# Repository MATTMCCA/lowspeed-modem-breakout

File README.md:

# DO NOT Screw with the telephone lines, the FCC will come after you...

(This IC dose have a transferable, Part 68 Registration. Since this board is not going to be evaluated for compliance, I advise you keep this puppy away from live phone lines.)

Hooking up unlicensed homebrew phone equipment is illegal, be smart, [just go buy a modem](https://www.newegg.com/p/2Z4-025W-02BE7).  

Could this be used with a Raspberry Pi or Arduino? Yes, Absolutely.  Just make sure you don't operate this device on the phone network without proper certs or permission from phone company (which I don't even think is a thing). 

[... I'm Serious](https://www.law.cornell.edu/uscode/text/47/227).

This may be a better [alt](https://www.tindie.com/products/theoldnet/rs232-serial-wifi-modem-for-vintage-computers-v3/).

# lowspeed-modem-breakout
Modem Module 2.4Kbps Data, BREAKOUT.

Not 56k, but it is an all in one solution with a super minimal part count.

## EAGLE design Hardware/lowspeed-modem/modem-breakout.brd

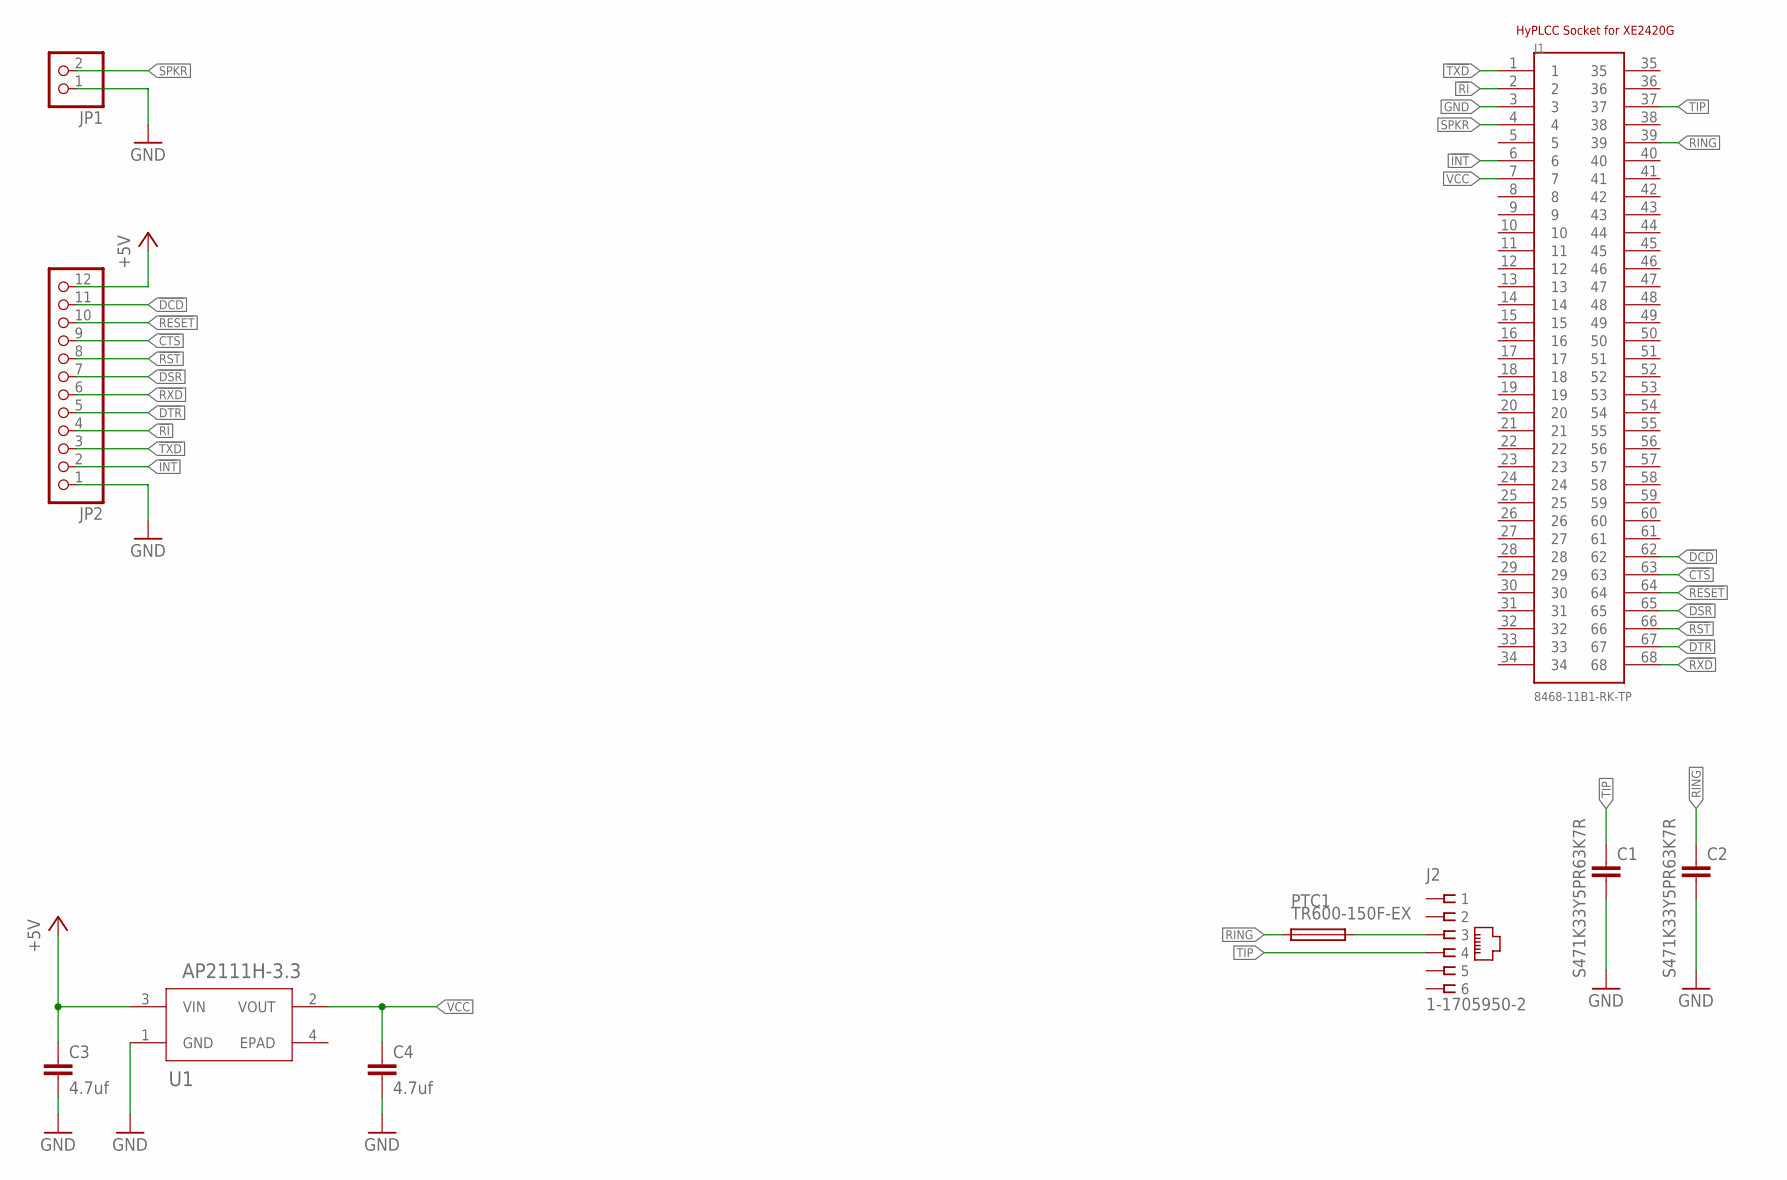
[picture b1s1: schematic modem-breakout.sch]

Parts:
C1, C2: S471K33Y5PR63K7R; C075-052X106
C3, C4: 4.7uf; C0805
J1: 8468-11B1-RK-TP; 3M_8468-11B1-RK-TP
J2: 1-1705950-2; RJ11-NO_SHIELD
JP1: PINHD-1X2; 1X02
JP2: PINHD-1X12; 1X12
PTC1: TR600-150F-EX; 13.50X6.00
U1: AP2111H-3.3; SOT-223_DIO-M

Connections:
!CTS: J1.63, JP2.9
!DCD: J1.62, JP2.11
!DSR: J1.65, JP2.7
!DTR: J1.67, JP2.5
!INT: J1.6, JP2.2
!RESET: J1.64, JP2.10
!RI: J1.2, JP2.4
!RST: J1.66, JP2.8
!RXD: J1.68, JP2.6
!TXD: J1.1, JP2.3
+5V: C3.1, JP2.12, U1.3 (VIN)
GND: C1.2, C2.2, C3.2, C4.2, J1.3, JP1.1, JP2.1, U1.1 (GND)
unnamed: J2.3, PTC1.P$2 (2)
RING: C2.1, J1.39, PTC1.P$1 (1)
SPKR: J1.4, JP1.2
TIP: C1.1, J1.37, J2.4
VCC: C4.1, J1.7, U1.2 (VOUT)

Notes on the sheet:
HyPLCC Socket for XE2420G

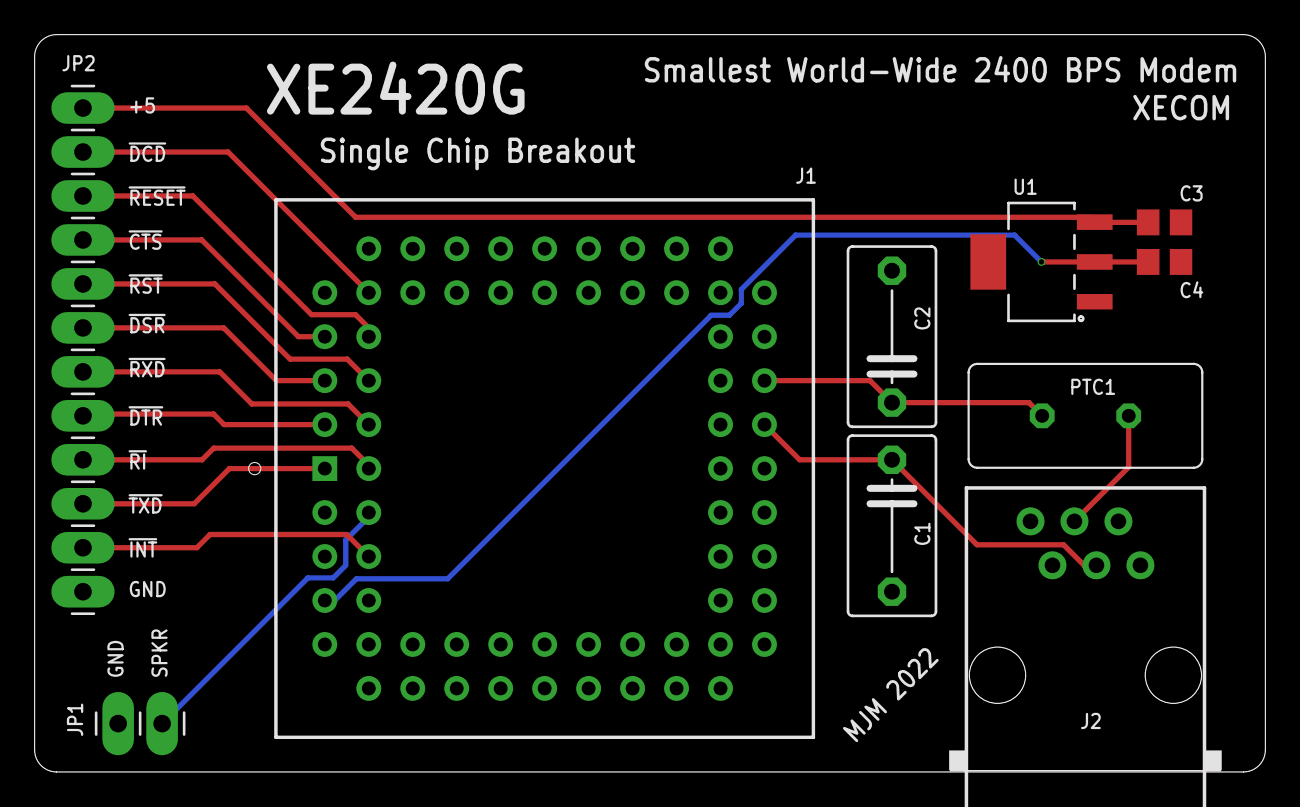
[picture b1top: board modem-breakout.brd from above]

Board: 2 copper layers, 71.1 x 42.6 mm, 10 parts (0 on the bottom side), 17 nets.

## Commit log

2022-01-01 FEAR THE FCC!
    init
2022-01-01 project
2022-01-01 nerp
2022-01-01 FCC Fear Part 2, Revenge of the FCC!
2022-01-02 added Gerbers for fab
